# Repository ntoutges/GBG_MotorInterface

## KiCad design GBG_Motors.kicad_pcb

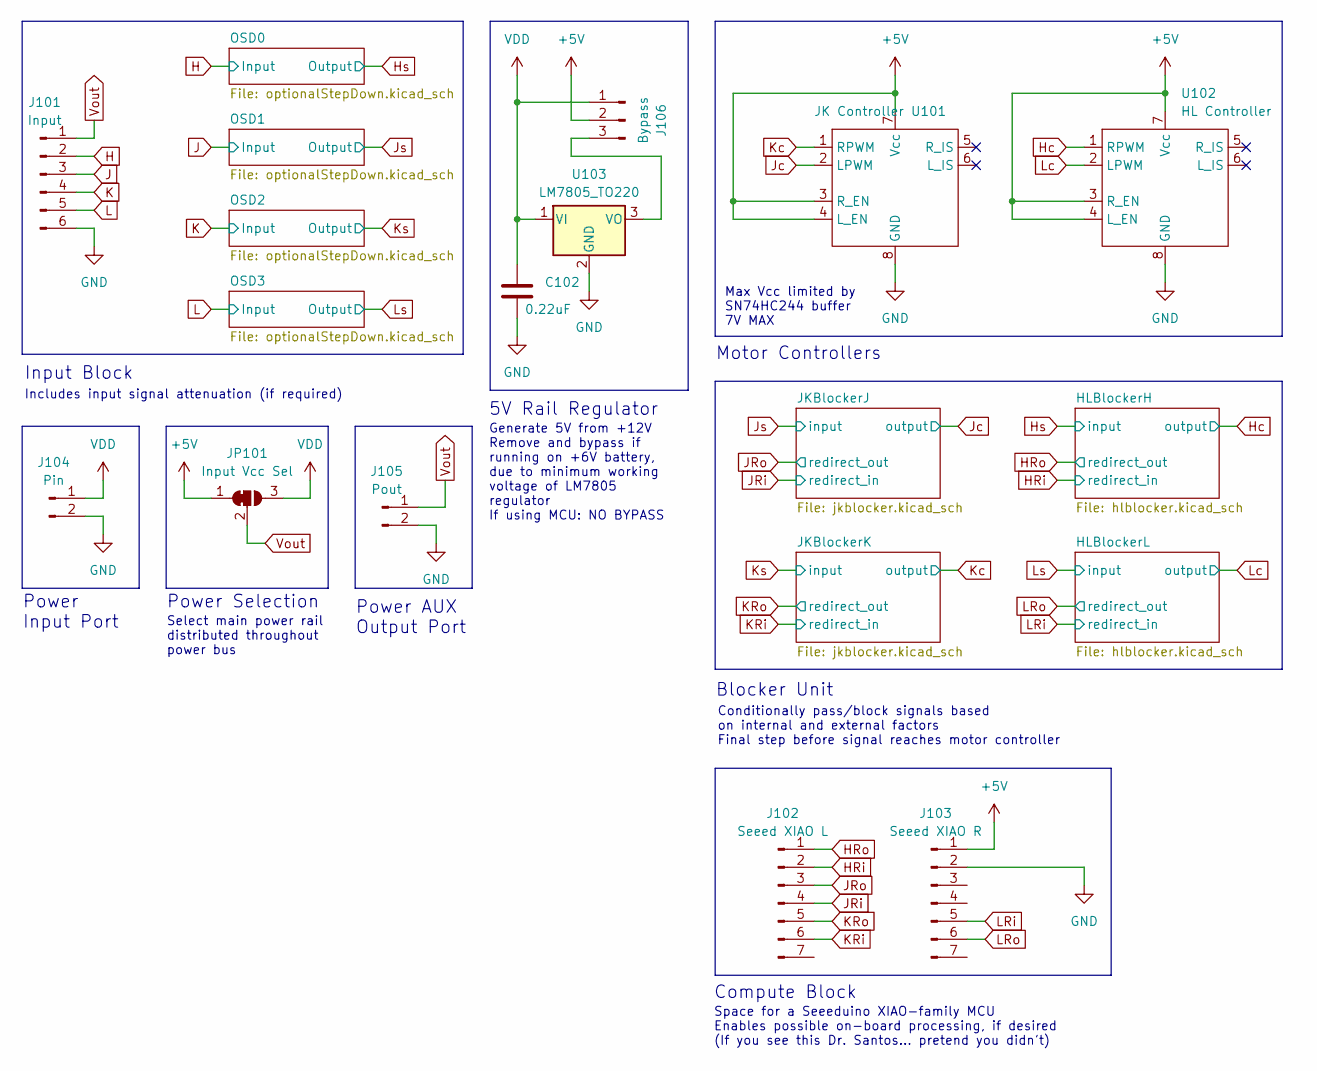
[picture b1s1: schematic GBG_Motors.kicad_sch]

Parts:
C102: 0.22uF; C_Axial_L3.8mm_D2.6mm_P7.50mm_Horizontal
J101: Input; PinHeader_1x06_P2.54mm_Vertical
J102: Seeed XIAO L; PinHeader_1x07_P2.54mm_Vertical
J103: Seeed XIAO R; PinHeader_1x07_P2.54mm_Vertical
J104: Pin; PinHeader_1x02_P2.54mm_Vertical
J105: Pout; PinHeader_1x02_P2.54mm_Vertical
J106: Bypass; PinHeader_1x03_P2.54mm_Vertical
JP101: Input Vcc Sel; SolderJumper-3_P1.3mm_Bridged12_RoundedPad1.0x1.5mm
U101: JK Controller; BTS7960
U102: HL Controller; BTS7960
U103: LM7805_TO220; TO-220-3_Vertical

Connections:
+5V: J103.1, J106.2, JP101.1 (A), U101.3 (R_EN), U101.4 (L_EN), U101.7 (Vcc), U102.3 (R_EN), U102.4 (L_EN), U102.7 (Vcc); also elsewhere on the board
GND: C102.2, J101.6, J103.2, J104.2, J105.2, U101.8 (GND), U102.8 (GND), U103.2 (GND); also elsewhere on the board
H: J101.2; also elsewhere on the board
HRi: J102.2; also elsewhere on the board
HRo: J102.1; also elsewhere on the board
Hc: U102.1 (RPWM); also elsewhere on the board
J: J101.3; also elsewhere on the board
JRi: J102.4; also elsewhere on the board
JRo: J102.3; also elsewhere on the board
Jc: U101.2 (LPWM); also elsewhere on the board
K: J101.4; also elsewhere on the board
KRi: J102.6; also elsewhere on the board
KRo: J102.5; also elsewhere on the board
Kc: U101.1 (RPWM); also elsewhere on the board
L: J101.5; also elsewhere on the board
LRi: J103.5; also elsewhere on the board
LRo: J103.6; also elsewhere on the board
Lc: U102.2 (LPWM); also elsewhere on the board
unnamed: J106.3, U103.3 (VO)
VDD: C102.1, J104.1, J106.1, JP101.3 (B), U103.1 (VI)
Vout: J101.1, J105.1, JP101.2 (C); also elsewhere on the board

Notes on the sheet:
Compute Block
Conditionally pass/block signals based on internal and external factors Final step before signal reaches motor controller
Input Block
Max Vcc limited by SN74HC244 buffer 7V MAX
Includes input signal attenuation (if required)
Power AUX Output Port
5V Rail Regulator
Space for a Seeeduino XIAO-family MCU Enables possible on-board processing, if desired (If you see this Dr. Santos... pretend you didn't)
Generate 5V from +12V Remove and bypass if running on +6V battery, due to minimum working voltage of LM7805 regulator If using MCU: NO BYPASS
Power Selection
Select main power rail distributed throughout power bus
Blocker Unit
Motor Controllers
Power Input Port

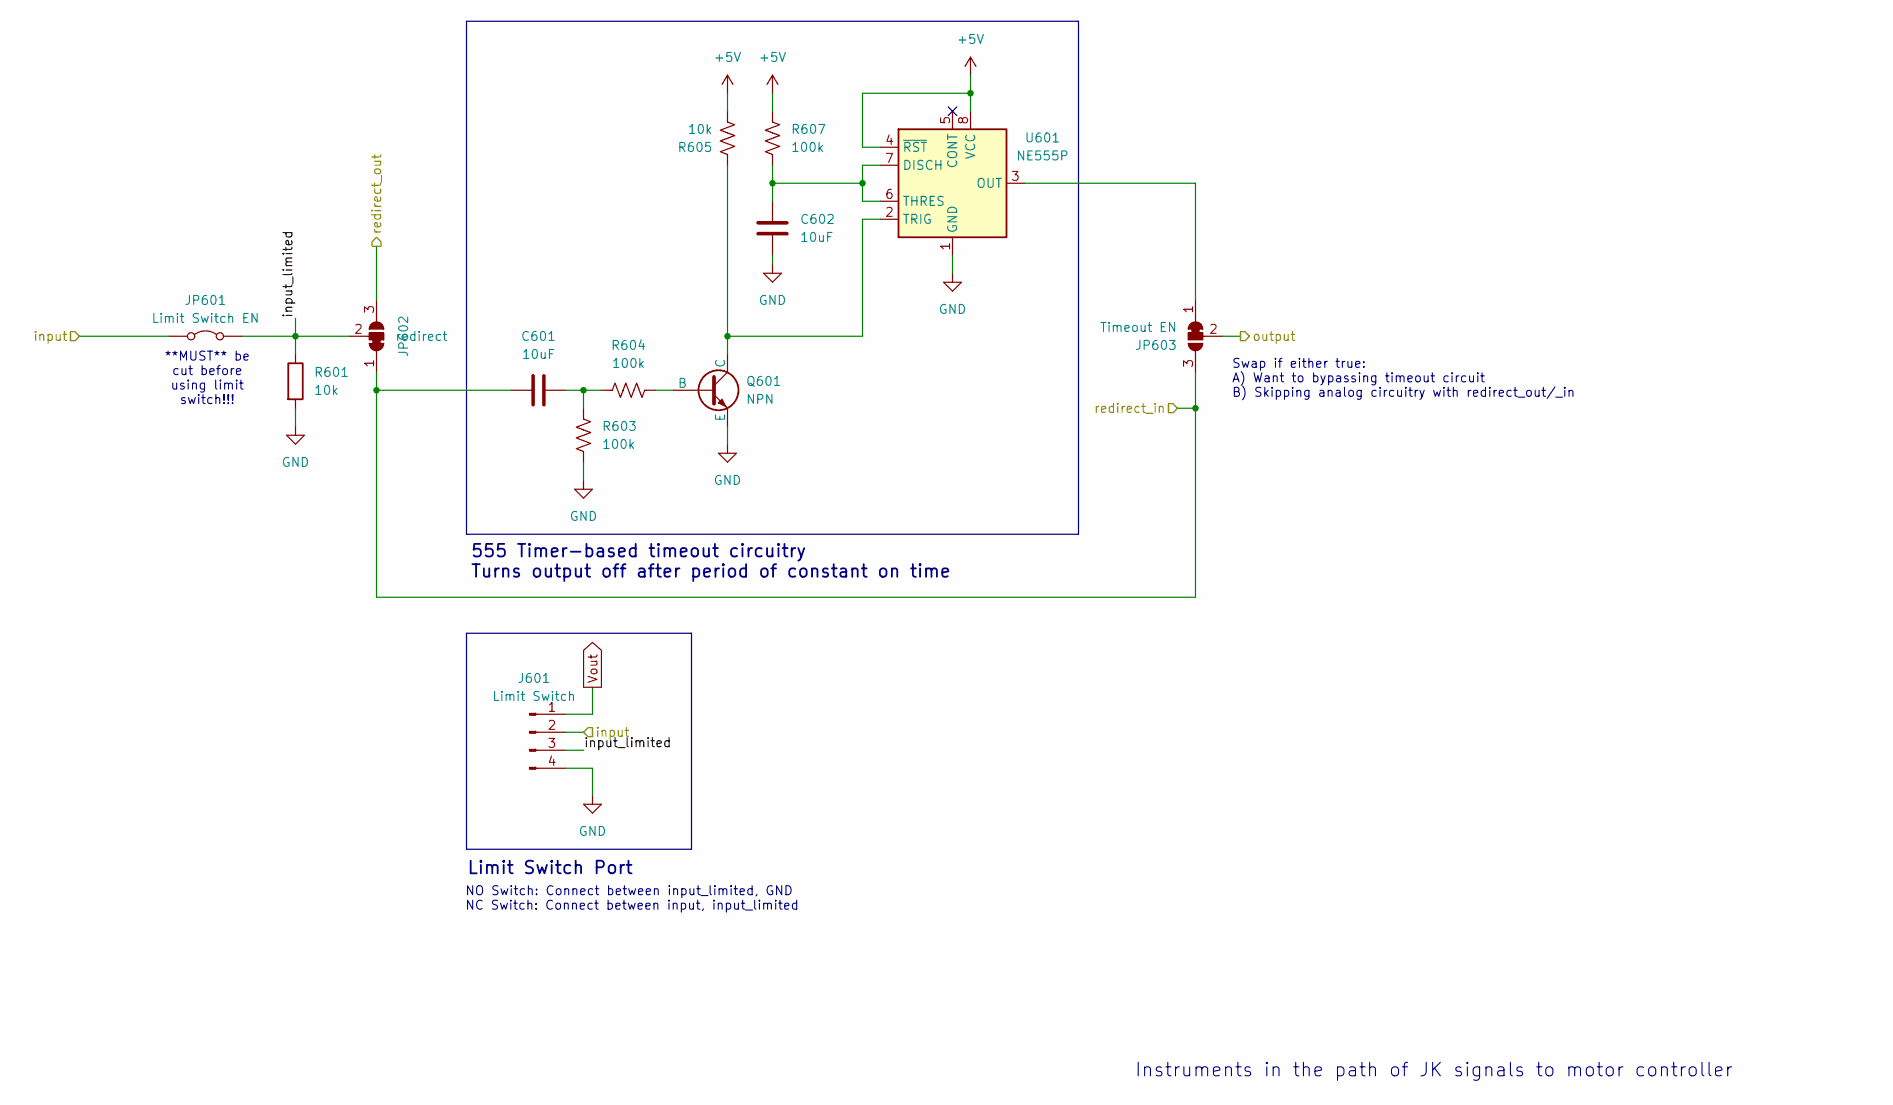
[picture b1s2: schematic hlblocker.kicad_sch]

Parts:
C601, C602: 10uF; C_Axial_L3.8mm_D2.6mm_P7.50mm_Horizontal
J601: Limit Switch; PinHeader_1x04_P2.54mm_Vertical
JP601: Limit Switch EN; SolderJumper-2_P1.3mm_Bridged_RoundedPad1.0x1.5mm
JP602: redirect; SolderJumper-3_P1.3mm_Bridged12_RoundedPad1.0x1.5mm
JP603: Timeout EN; SolderJumper-3_P1.3mm_Bridged12_RoundedPad1.0x1.5mm
Q601: NPN; TO-92_Wide
R601, R605: 10k; R_Axial_DIN0207_L6.3mm_D2.5mm_P7.62mm_Horizontal
R603, R604, R607: 100k; R_Axial_DIN0207_L6.3mm_D2.5mm_P7.62mm_Horizontal
U601: NE555P; DIP-8_W7.62mm

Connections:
+5V: R605.2, R607.1, U601.4 (~RST), U601.8 (VCC); also elsewhere on the board
/HLBlockerH/input_limited: J601.3, JP601.2 (B), JP602.2 (C), R601.1
GND: C602.2, J601.4, Q601.3 (E), R601.2, R603.2, U601.1 (GND); also elsewhere on the board
HRi: C601.1, JP602.1 (A), JP603.3 (B); also elsewhere on the board
HRo: JP602.3 (B); also elsewhere on the board
Hc: JP603.2 (C); also elsewhere on the board
Hs: J601.2, JP601.1 (A); also elsewhere on the board
unnamed: C601.2, R603.1, R604.1
unnamed: JP603.1 (A), U601.3 (OUT)
unnamed: Q601.2 (B), R604.2
unnamed: Q601.1 (C), R605.1, U601.2 (TRIG)
unnamed: C602.1, R607.2, U601.6 (THRES), U601.7 (DISCH)
Vout: J601.1; also elsewhere on the board

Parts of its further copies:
C701, C702: 10uF; C_Axial_L3.8mm_D2.6mm_P7.50mm_Horizontal
J701: Limit Switch; PinHeader_1x04_P2.54mm_Vertical
JP701: Limit Switch EN; SolderJumper-2_P1.3mm_Bridged_RoundedPad1.0x1.5mm
JP702: redirect; SolderJumper-3_P1.3mm_Bridged12_RoundedPad1.0x1.5mm
JP703: Timeout EN; SolderJumper-3_P1.3mm_Bridged12_RoundedPad1.0x1.5mm
Q701: NPN; TO-92_Wide
R701, R705: 10k; R_Axial_DIN0207_L6.3mm_D2.5mm_P7.62mm_Horizontal
R703, R704, R706: 100k; R_Axial_DIN0207_L6.3mm_D2.5mm_P7.62mm_Horizontal
U701: NE555P; DIP-8_W7.62mm

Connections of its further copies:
+5V: R705.2, R706.1, U701.4 (~RST), U701.8 (VCC); also elsewhere on the board
/HLBlockerL/input_limited: J701.3, JP701.2 (B), JP702.2 (C), R701.1
GND: C702.2, J701.4, Q701.3 (E), R701.2, R703.2, U701.1 (GND); also elsewhere on the board
LRi: C701.1, JP702.1 (A), JP703.3 (B); also elsewhere on the board
LRo: JP702.3 (B); also elsewhere on the board
Lc: JP703.2 (C); also elsewhere on the board
Ls: J701.2, JP701.1 (A); also elsewhere on the board
unnamed: C701.2, R703.1, R704.1
unnamed: JP703.1 (A), U701.3 (OUT)
unnamed: Q701.2 (B), R704.2
unnamed: Q701.1 (C), R705.1, U701.2 (TRIG)
unnamed: C702.1, R706.2, U701.6 (THRES), U701.7 (DISCH)
Vout: J701.1; also elsewhere on the board

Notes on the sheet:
**MUST** be cut before using limit switch!!!
555 Timer-based timeout circuitry Turns output off after period of constant on time
Instruments in the path of JK signals to motor controller
NO Switch: Connect between input_limited, GND NC Switch: Connect between input, input_limited
Limit Switch Port
Swap if either true: A) Want to bypassing timeout circuit B) Skipping analog circuitry with redirect_out/_in

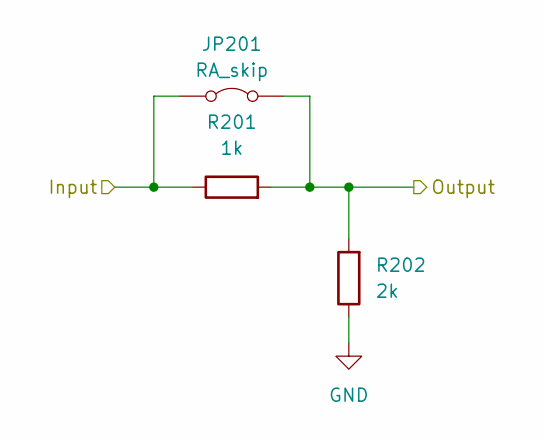
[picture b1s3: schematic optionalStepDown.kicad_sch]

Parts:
JP201: RA_skip; SolderJumper-2_P1.3mm_Bridged_RoundedPad1.0x1.5mm
R201: 1k; R_Axial_DIN0207_L6.3mm_D2.5mm_P7.62mm_Horizontal
R202: 2k; R_Axial_DIN0207_L6.3mm_D2.5mm_P7.62mm_Horizontal

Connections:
GND: R202.1; also elsewhere on the board
H: JP201.1 (A), R201.1; also elsewhere on the board
Hs: JP201.2 (B), R201.2, R202.2; also elsewhere on the board

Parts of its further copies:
JP301, JP401, JP501: RA_skip; SolderJumper-2_P1.3mm_Bridged_RoundedPad1.0x1.5mm
R301, R401, R501: 1k; R_Axial_DIN0207_L6.3mm_D2.5mm_P7.62mm_Horizontal
R302, R402, R502: 2k; R_Axial_DIN0207_L6.3mm_D2.5mm_P7.62mm_Horizontal

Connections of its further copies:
GND: R302.1, R402.1, R502.1; also elsewhere on the board
J: JP301.1 (A), R301.1; also elsewhere on the board
Js: JP301.2 (B), R301.2, R302.2; also elsewhere on the board
K: JP401.1 (A), R401.1; also elsewhere on the board
Ks: JP401.2 (B), R401.2, R402.2; also elsewhere on the board
L: JP501.1 (A), R501.1; also elsewhere on the board
Ls: JP501.2 (B), R501.2, R502.2; also elsewhere on the board

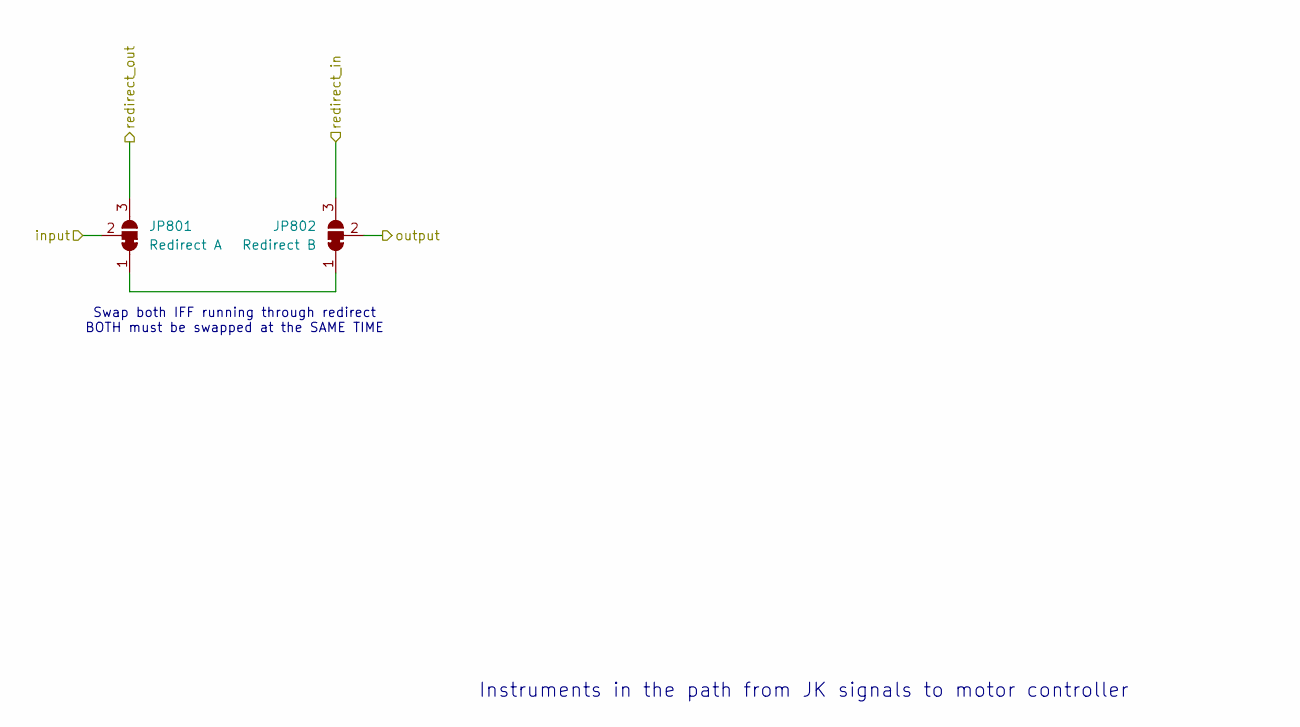
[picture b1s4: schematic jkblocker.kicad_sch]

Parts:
JP801: Redirect A; SolderJumper-3_P1.3mm_Bridged12_RoundedPad1.0x1.5mm
JP802: Redirect B; SolderJumper-3_P1.3mm_Bridged12_RoundedPad1.0x1.5mm

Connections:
JRi: JP802.3 (B); also elsewhere on the board
JRo: JP801.3 (B); also elsewhere on the board
Jc: JP802.2 (C); also elsewhere on the board
Js: JP801.2 (C); also elsewhere on the board
unnamed: JP801.1 (A), JP802.1 (A)

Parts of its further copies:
JP901: Redirect A; SolderJumper-3_P1.3mm_Bridged12_RoundedPad1.0x1.5mm
JP902: Redirect B; SolderJumper-3_P1.3mm_Bridged12_RoundedPad1.0x1.5mm

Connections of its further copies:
KRi: JP902.3 (B); also elsewhere on the board
KRo: JP901.3 (B); also elsewhere on the board
Kc: JP902.2 (C); also elsewhere on the board
Ks: JP901.2 (C); also elsewhere on the board
unnamed: JP901.1 (A), JP902.1 (A)

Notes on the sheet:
Instruments in the path from JK signals to motor controller
Swap both IFF running through redirect BOTH must be swapped at the SAME TIME

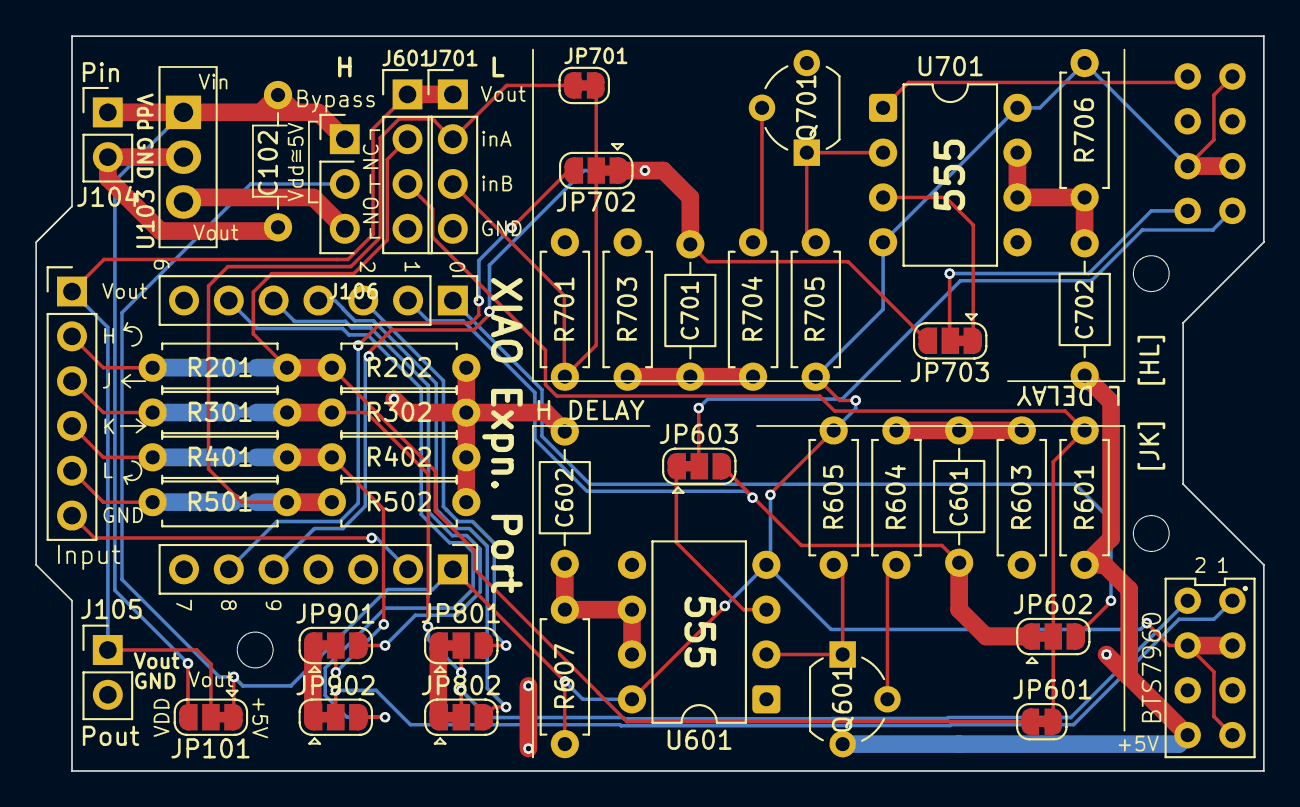
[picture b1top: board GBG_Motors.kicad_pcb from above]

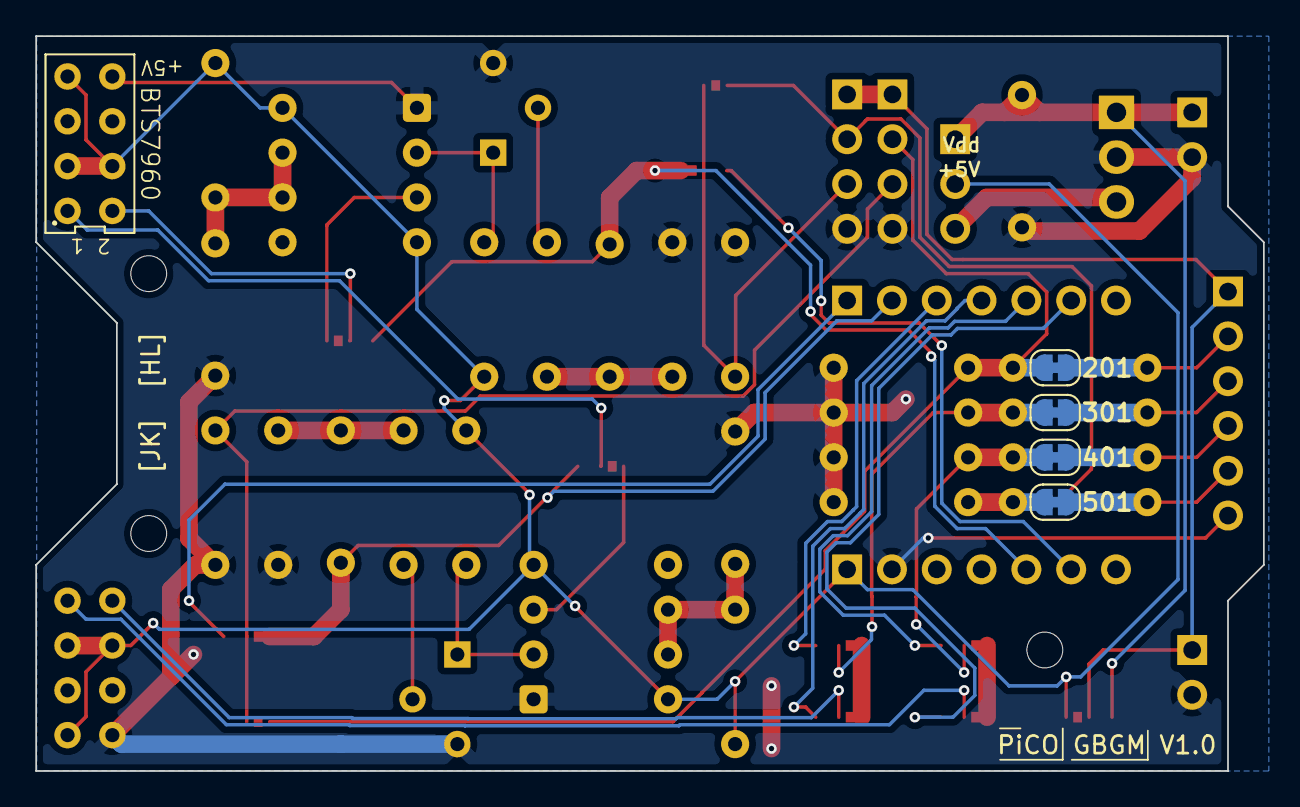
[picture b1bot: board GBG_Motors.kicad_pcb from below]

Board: 2 copper layers, 69.6 x 41.7 mm, 53 parts (5 on the bottom side), 39 nets.
